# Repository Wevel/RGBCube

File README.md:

# RGBCube
Project aiming to create a small led cube similar to that of [Greg Davill](https://gregdavill.com/blog/2020/6/13/miniature-3456x-led-cube). This will likely use the same [LED panels](https://github.com/gregdavill/GlassUnicorn/tree/master/hardware/panel_r0.1), but will require a new control board to account for what components are available.

## Control Board
* Change MCU to ESP32 module so as to add wifi connectivity and simplify PCB
* Change FPGA to use one of the following:
	* [Teensy 4.0](https://www.pjrc.com/store/teensy40.html): Not an FPGA, but probably still powerful enough
	* [iCEBreaker Bitsy](https://1bitsquared.com/products/icebreaker-bitsy): Not currently available, but uses the same footprint as the Teensy 4.0, so could be a future upgrade
	* [UPduino v3.1](https://tinyvision.ai/products/upduino-v3-0): May be too long
* Change IMU (Hopefully to the BNO055 if it is ever available again)

## Led Panel
This will likely use the same [LED panels](https://github.com/gregdavill/GlassUnicorn/tree/master/hardware/panel_r0.1) as Greg Davill.

## Frame
May try to 3d print something.

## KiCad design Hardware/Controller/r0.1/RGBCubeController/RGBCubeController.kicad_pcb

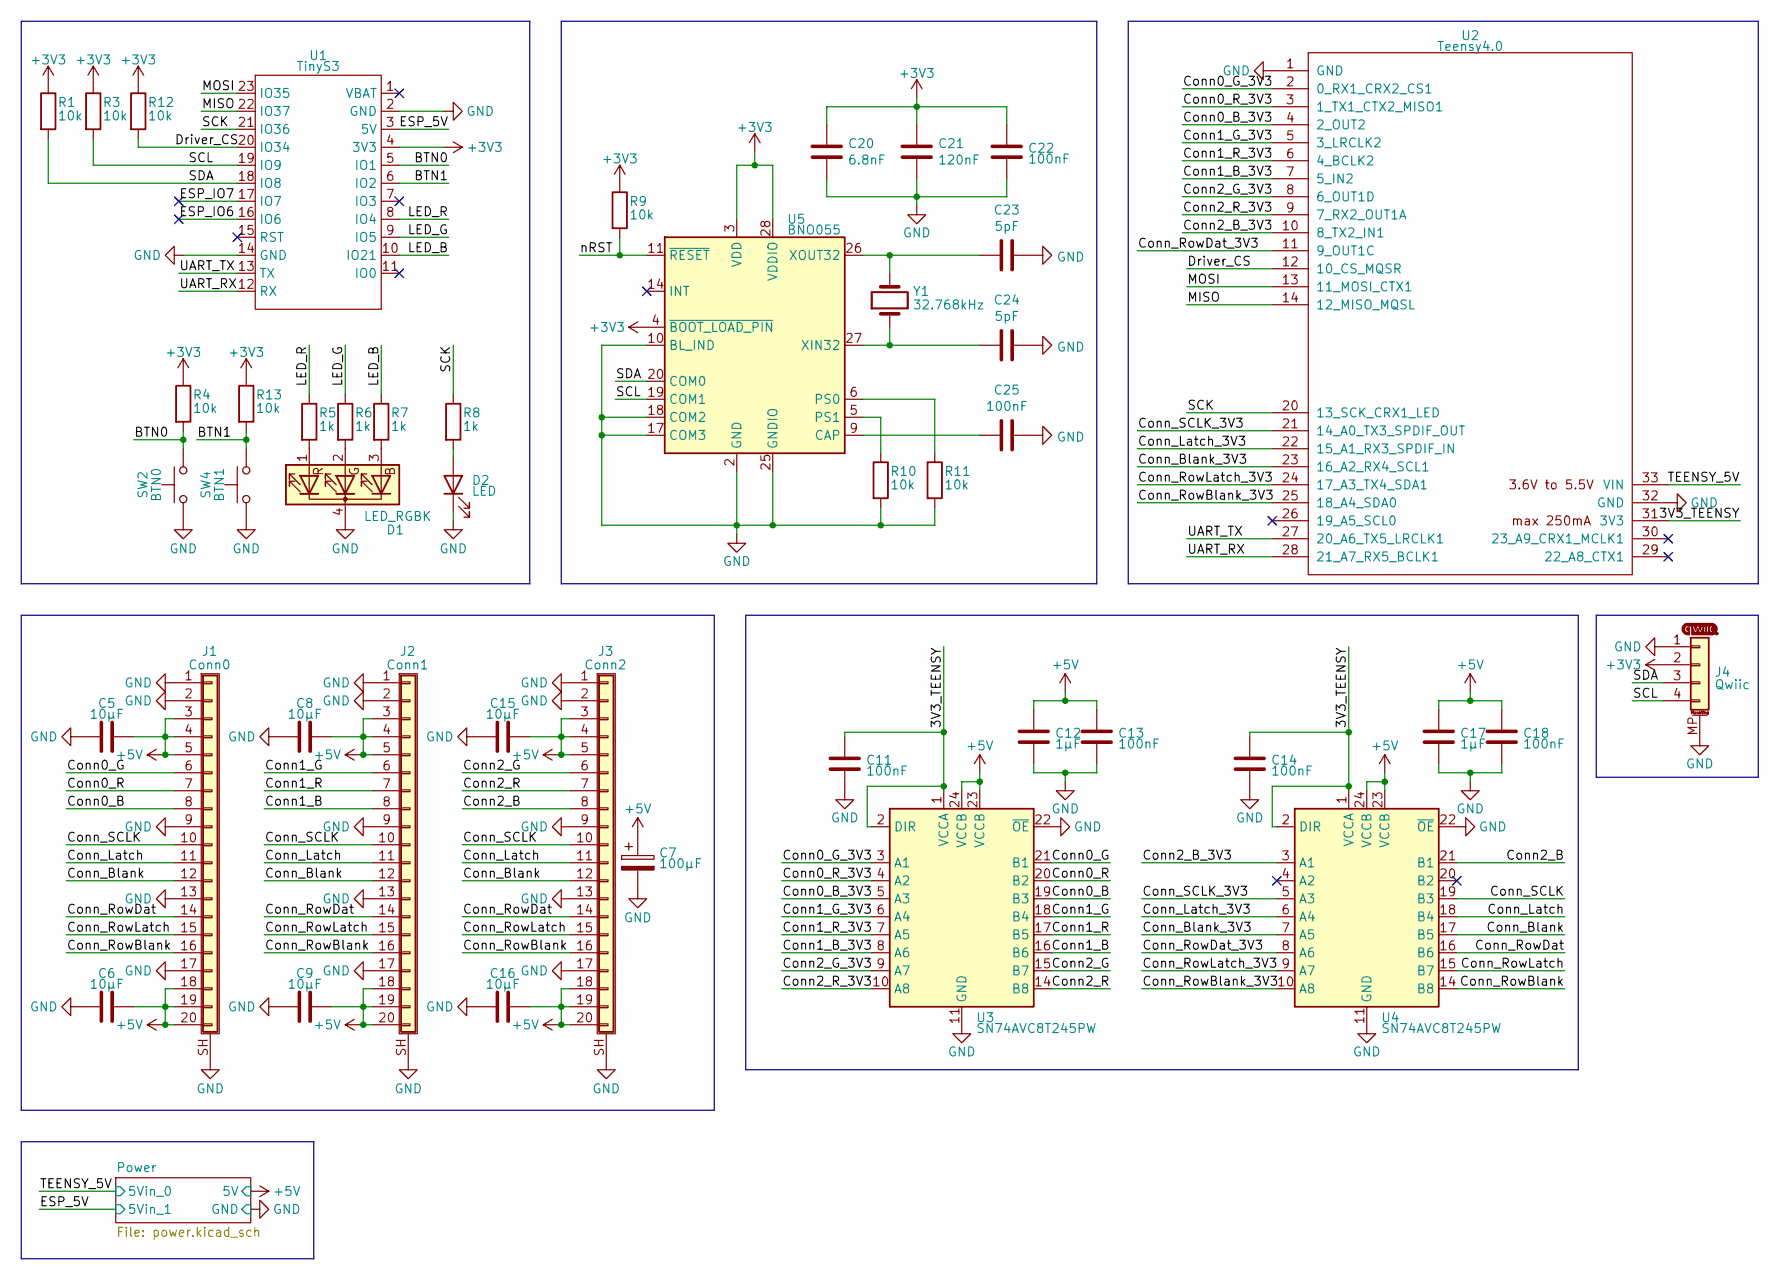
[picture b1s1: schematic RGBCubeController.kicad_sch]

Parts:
C5, C6, C8, C9, C15, C16: 10μF; C_0603_1608Metric
C7: 100μF; CP_Elec_5x3.9
C11, C13, C14, C18, C22, C25: 100nF; C_0603_1608Metric
C12, C17: 1μF; C_0603_1608Metric
C20: 6.8nF; C_0603_1608Metric
C21: 120nF; C_0603_1608Metric
C23, C24: 5pF; C_0402_1005Metric
D1: LED_RGBK; LED_Kingbright_AAA3528ESGCT
D2: LED; LED_0603_1608Metric
G1: LOGO; Qwiic
J1: Conn0; HRS_FH12-20S-0.5SVA(54)
J2: Conn1; HRS_FH12-20S-0.5SVA(54)
J3: Conn2; HRS_FH12-20S-0.5SVA(54)
J4: Qwiic; JST_SH_SM04B-SRSS-TB_1x04-1MP_P1.00mm_Horizontal
R1, R3, R4, R9, R10, R11, R12, R13: 10k; R_0603_1608Metric
R5, R6, R7, R8: 1k; R_0603_1608Metric
SW2: BTN0; PTS841_GKP
SW4: BTN1; PTS841_GKP
U1: TinyS3
U2: Teensy4.0; Teensy40_EdgesOnly
U3, U4: SN74AVC8T245PW; TSSOP-24_4.4x7.8mm_P0.65mm
U5: BNO055; LGA-28_5.2x3.8mm_P0.5mm
Y1: 32.768kHz; Crystal_SMD_3215-2Pin_3.2x1.5mm

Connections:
+3V3: C20.1, C21.1, C22.1, J4.2, R1.1, R3.1, R4.1, R9.1, R12.1, R13.1, U1.4 (3V3), U5.3 (VDD), U5.4 (~BOOT_LOAD_PIN), U5.28 (VDDIO)
+5V: C5.2, C6.2, C7.1, C8.2, C9.2, C12.2, C13.1, C15.2, C16.2, C17.2, C18.1, J1.3, J1.4, J1.5, J1.18, J1.19, J1.20, J2.3, J2.4, J2.5, J2.18, J2.19, J2.20, J3.3, J3.4, J3.5, J3.18, J3.19, J3.20, U3.23 (VCCB), U3.24 (VCCB), U4.23 (VCCB), U4.24 (VCCB); also elsewhere on the board
/3V3_TEENSY: C11.1, C14.1, U2.31 (3V3), U3.1 (VCCA), U3.2 (DIR), U4.1 (VCCA), U4.2 (DIR)
/BTN0: R4.2, SW2.2, U1.5 (IO1)
/BTN1: R13.2, SW4.2, U1.6 (IO2)
/Conn0_B: J1.8, U3.19 (B3)
/Conn0_B_3V3: U2.4 (2_OUT2), U3.5 (A3)
/Conn0_G: J1.6, U3.21 (B1)
/Conn0_G_3V3: U2.2 (0_RX1_CRX2_CS1), U3.3 (A1)
/Conn0_R: J1.7, U3.20 (B2)
/Conn0_R_3V3: U2.3 (1_TX1_CTX2_MISO1), U3.4 (A2)
/Conn1_B: J2.8, U3.16 (B6)
/Conn1_B_3V3: U2.7 (5_IN2), U3.8 (A6)
/Conn1_G: J2.6, U3.18 (B4)
/Conn1_G_3V3: U2.5 (3_LRCLK2), U3.6 (A4)
/Conn1_R: J2.7, U3.17 (B5)
/Conn1_R_3V3: U2.6 (4_BCLK2), U3.7 (A5)
/Conn2_B: J3.8, U4.21 (B1)
/Conn2_B_3V3: U2.10 (8_TX2_IN1), U4.3 (A1)
/Conn2_G: J3.6, U3.15 (B7)
/Conn2_G_3V3: U2.8 (6_OUT1D), U3.9 (A7)
/Conn2_R: J3.7, U3.14 (B8)
/Conn2_R_3V3: U2.9 (7_RX2_OUT1A), U3.10 (A8)
/Conn_Blank: J1.12, J2.12, J3.12, U4.17 (B5)
/Conn_Blank_3V3: U2.23 (16_A2_RX4_SCL1), U4.7 (A5)
/Conn_Latch: J1.11, J2.11, J3.11, U4.18 (B4)
/Conn_Latch_3V3: U2.22 (15_A1_RX3_SPDIF_IN), U4.6 (A4)
/Conn_RowBlank: J1.16, J2.16, J3.16, U4.14 (B8)
/Conn_RowBlank_3V3: U2.25 (18_A4_SDA0), U4.10 (A8)
/Conn_RowDat: J1.14, J2.14, J3.14, U4.16 (B6)
/Conn_RowDat_3V3: U2.11 (9_OUT1C), U4.8 (A6)
/Conn_RowLatch: J1.15, J2.15, J3.15, U4.15 (B7)
/Conn_RowLatch_3V3: U2.24 (17_A3_TX4_SDA1), U4.9 (A7)
/Conn_SCLK: J1.10, J2.10, J3.10, U4.19 (B3)
/Conn_SCLK_3V3: U2.21 (14_A0_TX3_SPDIF_OUT), U4.5 (A3)
/Driver_CS: R12.2, U1.20 (IO34), U2.12 (10_CS_MQSR)
/ESP_5V: U1.3 (5V); also elsewhere on the board
/ESP_IO6: U1.16 (IO6)
/ESP_IO7: U1.17 (IO7)
/LED_B: R7.1, U1.10 (IO21)
/LED_G: R6.1, U1.9 (IO5)
/LED_R: R5.1, U1.8 (IO4)
/MISO: U1.22 (IO37), U2.14 (12_MISO_MQSL)
/MOSI: U1.23 (IO35), U2.13 (11_MOSI_CTX1)
/SCK: R8.1, U1.21 (IO36), U2.20 (13_SCK_CRX1_LED)
/SCL: J4.4, R3.2, U1.19 (IO9), U5.19 (COM1)
/SDA: J4.3, R1.2, U1.18 (IO8), U5.20 (COM0)
/TEENSY_5V: U2.33 (VIN); also elsewhere on the board
/UART_RX: U1.12 (RX), U2.28 (21_A7_RX5_BCLK1)
/UART_TX: U1.13 (TX), U2.27 (20_A6_TX5_LRCLK1)
/nRST: R9.2, U5.11 (~RESET)
GND: C5.1, C6.1, C7.2, C8.1, C9.1, C11.2, C12.1, C13.2, C14.2, C15.1, C16.1, C17.1, C18.2, C20.2, C21.2, C22.2, C23.2, C24.2, C25.2, D1.4 (K), D2.1 (K), J1.1, J1.2, J1.9, J1.13, J1.17, J1.SH (Shield), J2.1, J2.2, J2.9, J2.13, J2.17, J2.SH (Shield), J3.1, J3.2, J3.9, J3.13, J3.17, J3.SH (Shield), J4.1, J4.MP (MountPin), R10.2, R11.2, SW2.1, SW4.1, U1.2 (GND), U1.14 (GND), U2.1 (GND), U2.32 (GND), U3.11 (GND), U3.12 (GND), U3.13 (GND), U3.22 (~OE), U4.11 (GND), U4.12 (GND), U4.13 (GND), U4.22 (~OE), U5.2 (GND), U5.10 (BL_IND), U5.15 (GNDIO), U5.16 (GNDIO), U5.17 (COM3), U5.18 (COM2), U5.25 (GNDIO); also elsewhere on the board
unnamed: D1.3 (BA), R7.2
unnamed: D1.2 (GA), R6.2
unnamed: D1.1 (RA), R5.2
unnamed: D2.2 (A), R8.2
unnamed: C25.1, U5.9 (CAP)
unnamed: R11.1, U5.6 (PS0)
unnamed: R10.1, U5.5 (PS1)
unnamed: C24.1, U5.27 (XIN32), Y1.1
unnamed: C23.1, U5.26 (XOUT32), Y1.2

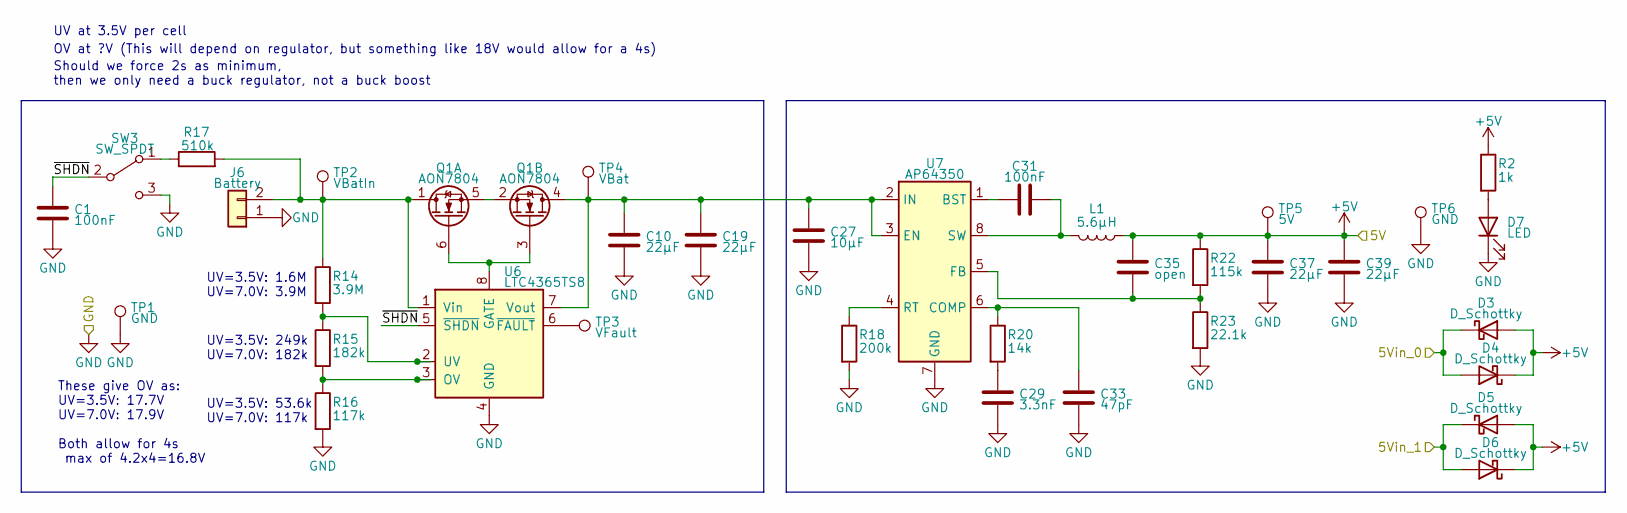
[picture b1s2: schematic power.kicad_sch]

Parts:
C1, C31: 100nF; C_0603_1608Metric
C10, C19, C37, C39: 22μF; C_0603_1608Metric
C27: 10μF; C_0603_1608Metric
C29: 3.3nF; C_0603_1608Metric
C33: 47pF; C_0603_1608Metric
C35: open; C_0603_1608Metric
D3, D4, D5, D6: D_Schottky; D_SOD-123F
D7: LED; LED_0603_1608Metric
J6: Battery; AMASS_XT30UPB-M_1x02_P5.0mm_Vertical
L1: 5.6μH; L_Bourns_SRN8040TA
Q1: AON7804; DFN3X3
R2: 1k; R_0603_1608Metric
R14: 3.9M; R_0603_1608Metric
R15: 182k; R_0603_1608Metric
R16: 117k; R_0603_1608Metric
R17: 510k; R_0603_1608Metric
R18: 200k; R_0603_1608Metric
R20: 14k; R_0603_1608Metric
R22: 115k; R_0603_1608Metric
R23: 22.1k; R_0603_1608Metric
SW3: SW_SPDT; SW_SPDT_PCM12
TP1, TP6: GND; TestPoint_Pad_D1.0mm
TP2: VBatIn; TestPoint_Pad_D1.0mm
TP3: VFault; TestPoint_Pad_D1.0mm
TP4: VBat; TestPoint_Pad_D1.0mm
TP5: 5V; TestPoint_Pad_D1.0mm
U6: LTC4365TS8; TSOT-23-8
U7: AP64350; Diodes_SO-8EP

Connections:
+5V: C35.1, C37.1, C39.1, D3.2 (A), D4.1 (K), D5.2 (A), D6.1 (K), L1.1, R2.1, R22.1, TP5.1; also elsewhere on the board
/ESP_5V: D5.1 (K), D6.2 (A); also elsewhere on the board
/Power/~SHDN: C1.2, SW3.2 (B), U6.5 (~SHDN)
/TEENSY_5V: D3.1 (K), D4.2 (A); also elsewhere on the board
GND: C1.1, C10.2, C19.2, C27.2, C29.2, C33.2, C37.2, C39.2, D7.1 (K), J6.1, R16.2, R18.2, R23.2, SW3.3 (C), TP1.1, TP6.1, U6.4 (GND), U7.7 (GND), U7.9 (EP); also elsewhere on the board
unnamed: C29.1, R20.2
unnamed: D7.2 (A), R2.2
unnamed: J6.2, Q1.1 (D), R14.1, R17.2, TP2.1, U6.1 (Vin)
unnamed: Q1.3 (G), Q1.6 (G), U6.8 (GATE)
unnamed: Q1.2 (S), Q1.5 (S)
unnamed: C10.1, C19.1, C27.1, Q1.4 (D), TP4.1, U6.7 (Vout), U7.2 (IN), U7.3 (EN)
unnamed: R17.1, SW3.1 (A)
unnamed: R15.2, R16.1, U6.3 (OV)
unnamed: R14.2, R15.1, U6.2 (UV)
unnamed: TP3.1, U6.6 (~FAULT)
unnamed: C31.1, U7.1 (BST)
unnamed: C33.1, R20.1, U7.6 (COMP)
unnamed: C35.2, R22.2, R23.1, U7.5 (FB)
unnamed: R18.1, U7.4 (RT)
unnamed: C31.2, L1.2, U7.8 (SW)

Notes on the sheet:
Should we force 2s as minimum, then we only need a buck regulator, not a buck boost
UV=3.5V: 1.6M UV=7.0V: 3.9M
UV=3.5V: 53.6k UV=7.0V: 117k
OV at ?V (This will depend on regulator, but something like 18V would allow for a 4s)
These give OV as: UV=3.5V: 17.7V UV=7.0V: 17.9V Both allow for 4s max of 4.2x4=16.8V
UV at 3.5V per cell
UV=3.5V: 249k UV=7.0V: 182k

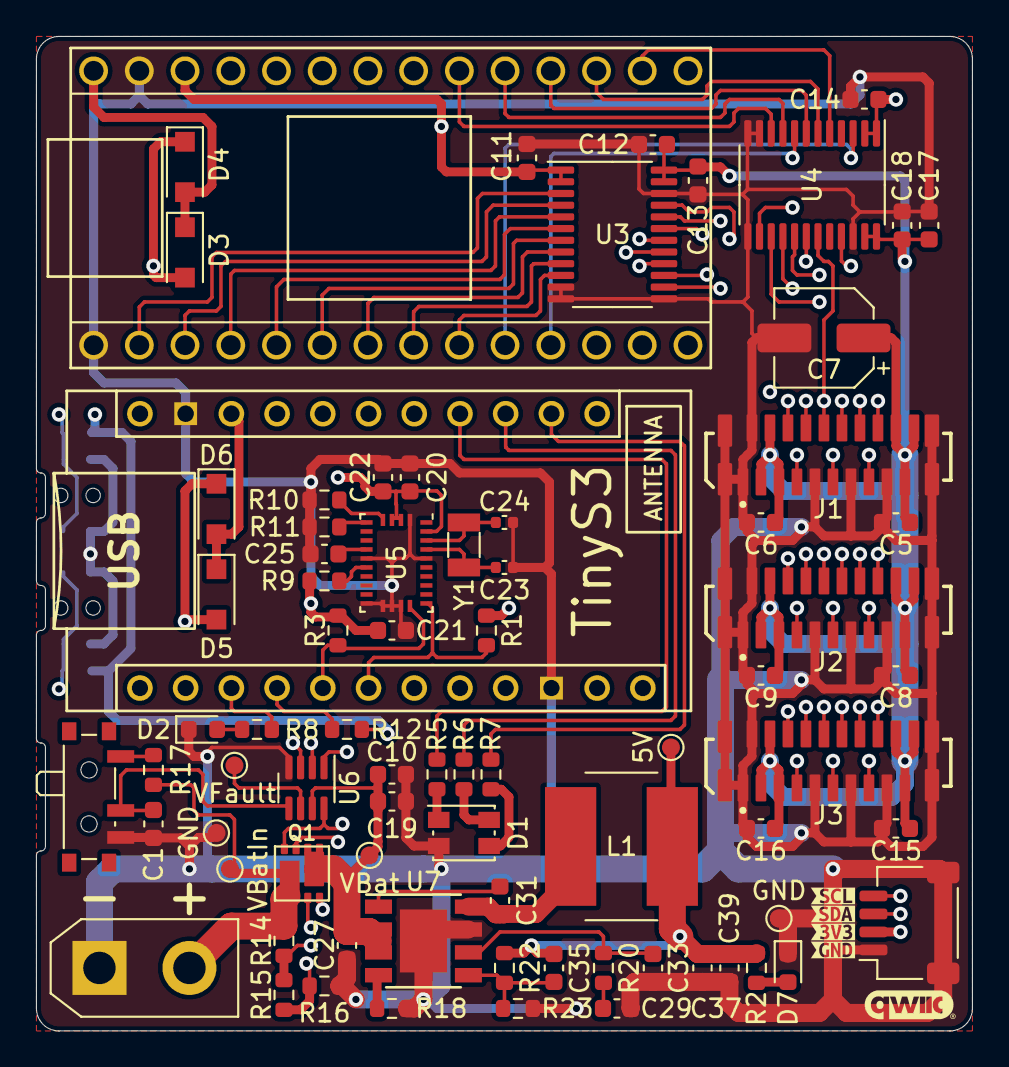
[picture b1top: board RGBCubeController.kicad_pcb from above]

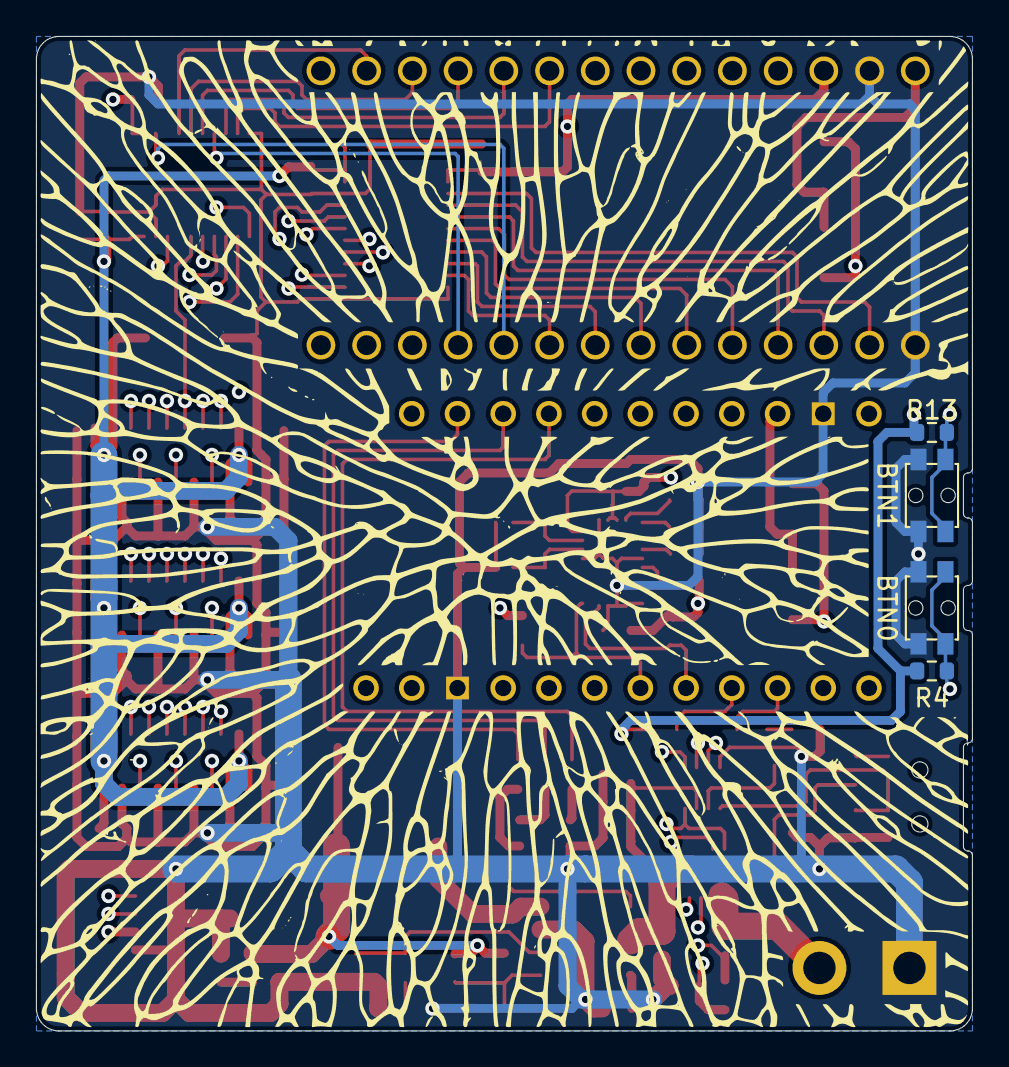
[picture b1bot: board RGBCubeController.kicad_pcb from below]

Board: 4 copper layers, 52.0 x 55.3 mm, 86 parts (4 on the bottom side), 75 nets.

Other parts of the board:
kibuzzard-621A4C97: G***; kibuzzard-621A4C97
kibuzzard-621A49AA: G***; kibuzzard-621A49AA
kibuzzard-621A49B5: G***; kibuzzard-621A49B5
kibuzzard-621A4989: G***; kibuzzard-621A4989

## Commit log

2022-02-08 [RGBCubeController] Completed schematic, and started on PCB.
2022-02-08 [RGBCubeController] Switched to using the Unexpected Maker TinyS3 ESP32 S3 dev board. This removes the need for a 3V3 regulator, reduces the number of components, as well as improving the main microc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
2022-02-09 [RGBCubeController] Added power off switch. There will still be ~10 - 20uA current draw when off, so battery should be disconnected for long term storage. Still need to route everything.
2022-02-27 [RGBCubeController] Added Qwiic connector, as well as a pattern to the silkscreen on backside of PCB.
